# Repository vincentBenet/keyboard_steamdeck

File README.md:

# keyboard_steamdeck

[Github](https://github.com/vincentBenet/keyboard_steamdeck)
[Author: Vincent Bénet](https://github.com/vincentBenet)

## Introduction

This project aim to create a minimalist custom keyboard using standard keycaps.
The goal is to have no keys restriction compare to a 120% keyboard.

## Features
Bellow a list of features of this keyboard:

    - All keys from 120% keyboards (Directionnal arrows, del, backspace, G keys)
    
    - Possibility to switch from AZERTY to QWERTY
    
    - 8 programables macro-G-keys
    
    - Up to 6 differents keys mapped on one switch (FN1, FN2, FN3, FN4, SHIFT, Simple press)
    
    - Reprogramming possibility of firmware
    
    - Electro Static Protection using TVS USB
    
    - Very low energy consumption using STM32L0 Chip
    
    - Case-material versatile (Wood, Aluminium, Inox, plastic, ...) (2mm cutted sheet)
    
## Layout

[Edit - Layout](http://www.keyboard-layout-editor.com/##@@_c=%23000000&t=%23ffffff&f:2%3B&=%F0%9F%94%8F%0A%E2%8F%8F%EF%B8%8F%0A%E2%9D%8C%0A%E2%8C%A8%0A%0A%0A%0A%0A%0AESC&_c=%23ff3b00&t=%234000ff%0A%2300ffde%0A%23337000&f:3%3B&=1%0AF1%0A%2F&%0A%C2%B2%0A%0A%0A%0A%0A%0AA&_c=%23000000&t=%23ffffff%0A%2300ffde%3B&=2%0AF2%0A%C3%A9%0A~%0A%0A%0A%0A%0A%0AZ&_c=%23ff3b00&t=%234000ff%0A%2300ffde%0A%23337000%3B&=3%0AF3%0A%22%0A%23%0A%0A%0A%0A%0A%0AE&=4%0AF4%0A'%0A%7B%0A%0A%0A%0A%0A%0AR&=5%0AF5%0A(%0A%5B%0A%0A%0A%0A%0A%0AT&=6%0AF6%0A-%0A%7C%0A%0A%0A%0A%0A%0AY&=7%0AF7%0A%C3%A8%0A%60%0A%0A%0A%0A%0A%0AU&=8%0AF8%0A%2F_%0A%5C%0A%0A%0A%0A%0A%0A%E2%85%A0&=9%0AF9%0A%C3%A7%0A%5E%0A%0A%0A%0A%0A%0AO&=0%0AF10%0A%C3%A0%0A%2F@%0A%0A%0A%0A%0A%0AP%3B&@_c=%233d3d3d&t=%23ffffff&a:7&f:9%3B&=%E2%87%84&_c=%23000000&a:4&f:3%3B&=(%0A%3C%0A%5B%0A%7B%0A%0A%0A%0A%0A%0AQ&=%C2%B6%0A-%0A%E2%84%B9%EF%B8%8F%0A%2F_%0A%0A%0A%0A%0A%0AS&=)%0A%3E%0A%5D%0A%7D%0A%0A%0A%0A%0A%0AD&_c=%230068ff&t=%23fff300%0A%0A%0A%0A%0A%0A%0A%0A%0A%2300ff17%3B&=G1%0AG3%0AG2%0AG4%0A%0A%0A%0A%0A%0AF&_t=%23a32424%0A%0A%0A%23ff0000%0A%0A%0A%0A%0A%0A%2300ff17%3B&=%E2%8F%BA%0A%F0%9F%8E%AC%0A%F0%9F%8E%A4%0A%E2%8F%B9%0A%0A%0A%0A%0A%0AG&_t=%23fff300%0A%0A%0A%0A%0A%0A%0A%0A%0A%2300ff17%3B&=G5%0AG7%0AG6%0AG8%0A%0A%0A%0A%0A%0AH&_c=%233c4225&t=%23ffffff%3B&=%C2%A5%0A%C3%B9%0A%C2%A4%0A%C2%B5%0A%0A%0A%0A%0A%0AJ&_c=%23a7a800&t=%23000000%3B&=%E2%82%AC%0A%C2%A2%0A$%0A%C2%A3%0A%0A%0A%0A%0A%0AK&_c=%23ff3b00&t=%23000000%0A%2300ffde%0A%23337000%3B&=%C2%B0%0AF12%0A%2F=%0A%7D%0A%0A%0A%0A%0A%0AL&=+%0AF11%0A)%0A%5D%0A%0A%0A%0A%0A%0AM%3B&@_c=%233d3d3d&t=%23ffffff&a:7&f:9%3B&=%E2%86%91&_c=%23ffa31a&t=%23000000&a:4&f:3%3B&=%E2%8C%A7%0A%C2%AB%0A%F0%9F%94%9E%0A%C2%BB%0A%0A%0A%0A%0A%0AW&_c=%238c1b00%3B&=%E2%9E%97%0A%E2%9E%96%0A%E2%9C%96%EF%B8%8F%0A%E2%9E%95%0A%0A%0A%0A%0A%0AX&_c=%23ffffff%3B&=%2F=%0A%EF%BC%85%0A%3F%0A%EF%B9%90%0A%0A%0A%0A%0A%0AC&=%C2%BF%0A%C3%A6%0A%E2%80%A7%0A%EF%BC%9B%0A%0A%0A%0A%0A%0AV&=%5C%0A%7C%0A%2F%2F%0A%EF%BC%9A%0A%0A%0A%0A%0A%0AB&=%E2%80%9C%0A%E2%80%9E%0A%C2%A7%0A!%0A%0A%0A%0A%0A%0AN&_c=%230bff00%3B&=%E2%8F%AB%0A%F0%9F%94%86%0A%F0%9F%92%BE%0A%F0%9F%94%8A%0A%0A%0A%0A%0A%0A%E2%96%B2&_c=%23ff00e8%3B&=%F0%9F%93%B7%0A%E2%AC%91%0A%F0%9F%94%91%0A%F0%9F%94%92%0A%0A%0A%0A%0A%0A%E2%8F%8E&_c=%23000000&t=%23ffffff%3B&=%E2%8C%9C%0A%0A%0A%0A%0A%0A%0A%0A%0AFN1&=%0A%0A%E2%8C%9D%0A%0A%0A%0A%0A%0A%0AFN2%3B&@_c=%23878787&a:7%3B&=CRTL&_c=%23000000&f:9%3B&=%F0%9F%97%BA%EF%B8%8F&_c=%238e8e8e&f:3%3B&=ALT&_c=%23000bff&a:4%3B&=%E2%9C%82%EF%B8%8F%0A%F0%9F%93%9D%0A%F0%9F%93%8B%0A%F0%9F%93%8C%0A%0A%0A%0A%0A%0A%E2%80%95&_c=%23ff00e8&t=%23000000%3B&=%E2%A4%BA%0A%E2%98%8E%0A%E2%8F%AE%0A%E2%8F%B9%0A%0A%0A%0A%0A%0A%E2%8C%AB&=%E2%A4%BC%0A%E2%9A%99%EF%B8%8F%0A%E2%8F%AD%0A%E2%8F%AF%0A%0A%0A%0A%0A%0A%E2%8C%A6&_c=%230bff00%3B&=%E2%8F%AA%0A%F0%9F%8C%93%0A%E2%9C%88%0A%F0%9F%94%87%0A%0A%0A%0A%0A%0A%E2%97%84&=%E2%8F%AC%0A%F0%9F%94%85%0A%F0%9F%93%85%0A%F0%9F%94%89%0A%0A%0A%0A%0A%0A%E2%96%BC&=%E2%8F%A9%0A%E2%9C%89%0A%F0%9F%93%B6%0A%E2%99%AB%0A%0A%0A%0A%0A%0A%E2%96%BA&_c=%23000000&t=%23ffffff%3B&=%0A%E2%8C%9E%0A%0A%0A%0A%0A%0A%0A%0AFN3&=%0A%0A%0A%E2%8C%9F%0A%0A%0A%0A%0A%0AFN4)

## Model 3D

## Schematic

## Routing

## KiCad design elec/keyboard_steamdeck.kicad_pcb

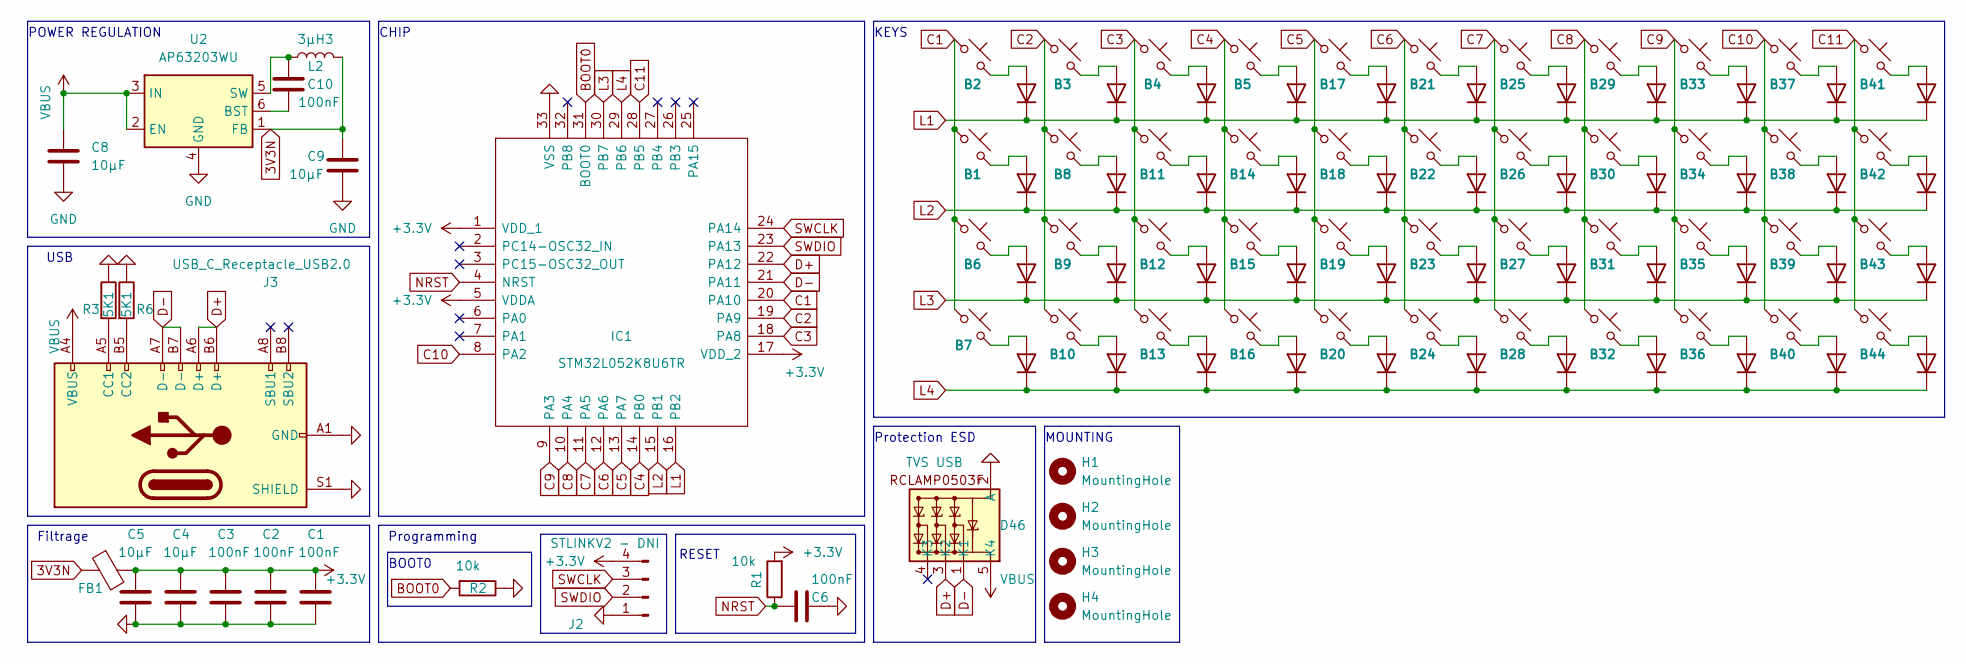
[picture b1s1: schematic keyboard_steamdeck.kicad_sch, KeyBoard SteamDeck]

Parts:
B1, B2, B3, B4, B5, B6, B7, B8, B9, B10, B11, B12, B13, B14, B15, B16, B17, B18, B19, B20, B21, B22, B23, B24, B25, B26, B27, B28, B29, B30, B31, B32, B33, B34, B35, B36, B37, B38, B39, B40, B41, B42, B43, B44: MX_SW_solder - DNI; SW_Cherry_MX_1.00u_PCB; MPN MX2A-L1NN
C1, C2, C3, C6, C10: 100nF; C_0402_1005Metric; MPN CC0402KRX7R8BB104
C4, C5, C8, C9: 10µF; C_0805_2012Metric; MPN CAP0805 X7R 10UF 10% 16V
D1, D2, D3, D4, D5, D6, D7, D8, D9, D10, D11, D12, D13, D14, D15, D16, D17, D18, D19, D20, D21, D22, D23, D24, D25, D26, D27, D28, D29, D30, D31, D32, D33, D34, D35, D36, D37, D38, D39, D40, D41, D42, D43, D44: 1N4148WX-TP; D_SOD-323_HandSoldering; MPN 1N4148WX-TP
D46: TVS USB; SOT-353_SC-70-5; MPN RCLAMP0503F.TCT
FB1: FerriteBead; R_0402_1005Metric; MPN PE-0603PFB121ST
H1, H2, H3, H4: MountingHole; MountingHole_3.2mm_M3
IC1: STM32L052K8U6TR; UFQFPN32-5x5mm; MPN STM32L052K8U6TR
J2: STLINKV2 - DNI; PinHeader_1x04_P2.54mm_Vertical; MPN 61300411121
J3: USB_C_Receptacle_USB2.0; USB C 2130830005; MPN 2130830005
L2: 3µH3; R_0805_2012Metric; MPN MLZ2012N3R3LT000
R1, R2: 10k; R_0402_1005Metric; MPN ERA-2AEB103X
R3, R6: 5K1; R_0402_1005Metric; MPN RN73R1ETTP5101B25
U2: AP63203WU; TSOT-23-6; MPN AP63203WU-7

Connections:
3V3N: C9.1, FB1.1, L2.2, U2.1 (FB)
+3.3V: C1.2, C2.2, C3.2, C4.2, C5.2, FB1.2, IC1.1 (VDD_1), IC1.5 (VDDA), IC1.17 (VDD_2), J2.4, R1.2
BOOT0: IC1.31 (BOOT0), R2.2
C1: B1.1, B2.1, B6.1, B7.1, IC1.20 (PA10)
C2: B3.1, B8.1, B9.1, B10.1, IC1.19 (PA9)
C3: B4.1, B11.1, B12.1, B13.1, IC1.18 (PA8)
C4: B5.1, B14.1, B15.1, B16.1, IC1.14 (PB0)
C5: B17.1, B18.1, B19.1, B20.1, IC1.13 (PA7)
C6: B21.1, B22.1, B23.1, B24.1, IC1.12 (PA6)
C7: B25.1, B26.1, B27.1, B28.1, IC1.11 (PA5)
C8: B29.1, B30.1, B31.1, B32.1, IC1.10 (PA4)
C9: B33.1, B34.1, B35.1, B36.1, IC1.9 (PA3)
C10: B37.1, B38.1, B39.1, B40.1, IC1.8 (PA2)
C11: B41.1, B42.1, B43.1, B44.1, IC1.28 (PB5)
D+: D46.3 (K2), IC1.22 (PA12), J3.A6 (D+), J3.B6 (D+)
D-: D46.1 (K1), IC1.21 (PA11), J3.A7 (D-), J3.B7 (D-)
GND: C1.1, C2.1, C3.1, C4.1, C5.1, C6.1, C8.2, C9.2, D46.2 (A), IC1.33 (VSS), J2.1, J3.A1 (GND), J3.A12 (GND), J3.B1 (GND), J3.B12 (GND), J3.S1 (SHIELD), R2.1, R3.1, R6.1, U2.4 (GND)
L1: D11.1 (K), D12.1 (K), D13.1 (K), D14.1 (K), D15.1 (K), D16.1 (K), D17.1 (K), D18.1 (K), D19.1 (K), D20.1 (K), D41.1 (K), IC1.16 (PB2)
L2: D1.1 (K), D2.1 (K), D3.1 (K), D4.1 (K), D5.1 (K), D6.1 (K), D7.1 (K), D8.1 (K), D9.1 (K), D10.1 (K), D42.1 (K), IC1.15 (PB1)
L3: D21.1 (K), D23.1 (K), D25.1 (K), D27.1 (K), D29.1 (K), D31.1 (K), D33.1 (K), D35.1 (K), D37.1 (K), D39.1 (K), D43.1 (K), IC1.30 (PB7)
L4: D22.1 (K), D24.1 (K), D26.1 (K), D28.1 (K), D30.1 (K), D32.1 (K), D34.1 (K), D36.1 (K), D38.1 (K), D40.1 (K), D44.1 (K), IC1.29 (PB6)
NRST: C6.2, IC1.4 (NRST), R1.1
unnamed: B22.2, D1.2 (A)
unnamed: B26.2, D2.2 (A)
unnamed: B30.2, D3.2 (A)
unnamed: B34.2, D4.2 (A)
unnamed: B38.2, D5.2 (A)
unnamed: B1.2, D6.2 (A)
unnamed: B8.2, D7.2 (A)
unnamed: B11.2, D8.2 (A)
unnamed: B14.2, D9.2 (A)
unnamed: B18.2, D10.2 (A)
unnamed: B2.2, D11.2 (A)
unnamed: B3.2, D12.2 (A)
unnamed: B4.2, D13.2 (A)
unnamed: B5.2, D14.2 (A)
unnamed: B17.2, D15.2 (A)
unnamed: B21.2, D16.2 (A)
unnamed: B25.2, D17.2 (A)
unnamed: B29.2, D18.2 (A)
unnamed: B33.2, D19.2 (A)
unnamed: B37.2, D20.2 (A)
unnamed: B6.2, D21.2 (A)
unnamed: B7.2, D22.2 (A)
unnamed: B9.2, D23.2 (A)
unnamed: B10.2, D24.2 (A)
unnamed: B12.2, D25.2 (A)
unnamed: B13.2, D26.2 (A)
unnamed: B15.2, D27.2 (A)
unnamed: B16.2, D28.2 (A)
unnamed: B19.2, D29.2 (A)
unnamed: B20.2, D30.2 (A)
unnamed: B23.2, D31.2 (A)
unnamed: B24.2, D32.2 (A)
unnamed: B27.2, D33.2 (A)
unnamed: B28.2, D34.2 (A)
unnamed: B31.2, D35.2 (A)
unnamed: B32.2, D36.2 (A)
unnamed: B35.2, D37.2 (A)
unnamed: B36.2, D38.2 (A)
unnamed: B39.2, D39.2 (A)
unnamed: B40.2, D40.2 (A)
unnamed: B41.2, D41.2 (A)
unnamed: B42.2, D42.2 (A)
unnamed: B43.2, D43.2 (A)
unnamed: B44.2, D44.2 (A)
unnamed: J3.A5 (CC1), R3.2
unnamed: J3.B5 (CC2), R6.2
unnamed: C10.2, U2.6 (BST)
unnamed: C10.1, L2.1, U2.5 (SW)
SWCLK: IC1.24 (PA14), J2.3
SWDIO: IC1.23 (PA13), J2.2
VBUS: C8.1, D46.5 (K4), J3.A4 (VBUS), J3.A9 (VBUS), J3.B4 (VBUS), J3.B9 (VBUS), U2.2 (EN), U2.3 (IN)

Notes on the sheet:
CHIP
Filtrage
KEYS
MOUNTING
POWER REGULATION
RESET
BOOT0
Protection ESD
USB
Programming

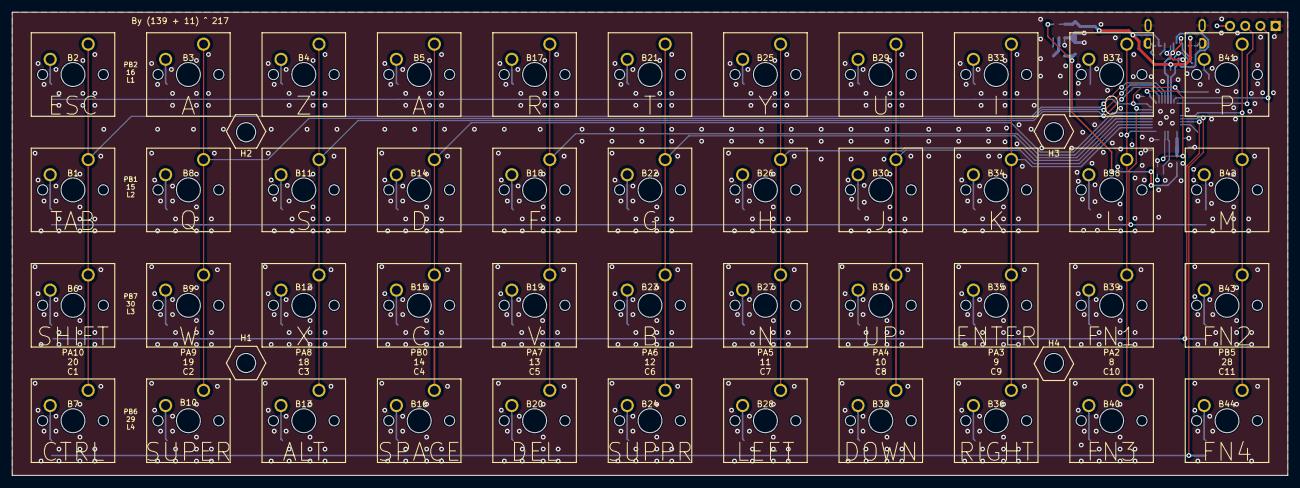
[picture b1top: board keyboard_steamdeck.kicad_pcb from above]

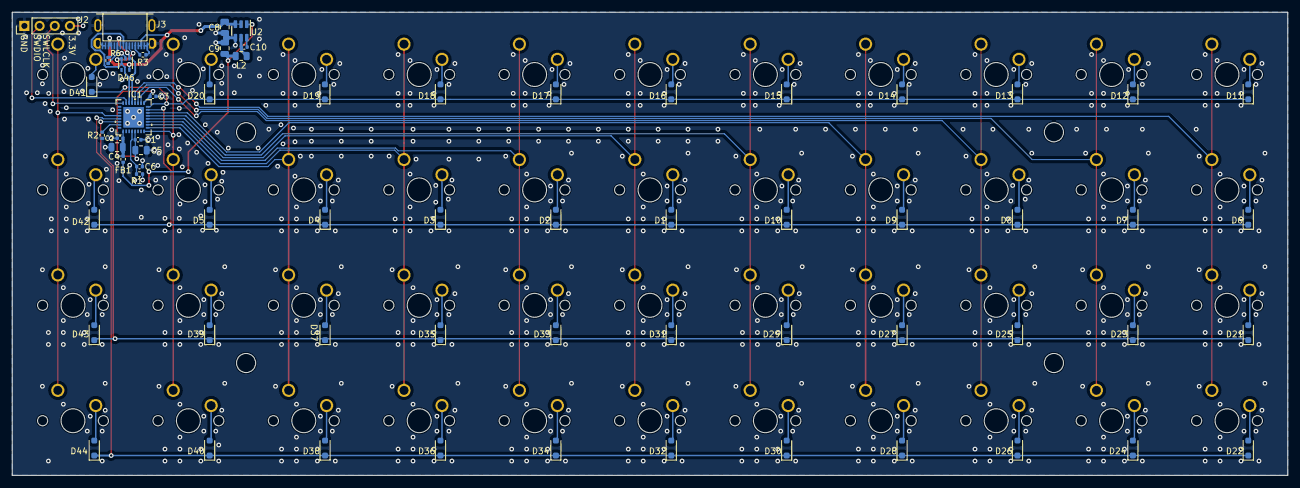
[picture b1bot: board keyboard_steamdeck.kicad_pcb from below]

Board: 4 copper layers, 213.4 x 77.5 mm, 112 parts (64 on the bottom side), 73 nets.

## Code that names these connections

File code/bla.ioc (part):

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Mcu.Name=STM32L052K(6-8)Ux
Mcu.Package=UFQFPN32
Mcu.UserName=STM32L052K8Ux
PA10.Signal=GPIO_Output
PA11.Mode=Device
PA11.Signal=USB_DM
PA12.Mode=Device
PA12.Signal=USB_DP
PA13.Mode=Serial_Wire
PA13.Signal=SYS_SWDIO
PA14.Mode=Serial_Wire
PA14.Signal=SYS_SWCLK
PA2.Signal=GPIO_Output
PA3.Signal=GPIO_Output
PA4.Signal=GPIO_Output
PA5.Signal=GPIO_Output
PA6.Signal=GPIO_Output
PA7.Signal=GPIO_Output
PA8.Signal=GPIO_Output
PA9.Signal=GPIO_Output
PB0.Signal=GPIO_Output
PB1.GPIOParameters=GPIO_PuPd
PB1.GPIO_PuPd=GPIO_PULLDOWN
PB1.Signal=GPIO_Input
PB2.GPIOParameters=GPIO_PuPd
PB2.GPIO_PuPd=GPIO_PULLDOWN
PB2.Signal=GPIO_Input
PB5.Signal=GPIO_Output
PB6.GPIOParameters=GPIO_PuPd
PB6.GPIO_PuPd=GPIO_PULLDOWN
PB6.Signal=GPIO_Input
PB7.GPIOParameters=GPIO_PuPd
PB7.GPIO_PuPd=GPIO_PULLDOWN
PB7.Signal=GPIO_Input
RCC.SYSCLKFreq_VALUE=24000000
RCC.SYSCLKSource=RCC_SYSCLKSOURCE_PLLCLK
board=custom

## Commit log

2023-10-10 corrections
2023-10-11 Finish
2023-10-11 readme
2023-10-13 ready to order PCB
2023-11-25 add_code
2024-01-09 working_key_scan
2024-01-31 working_keyboard
2024-02-10 Keyboard in FR + True repeating keys
2024-02-10 fix FN infinite repeat
2024-02-19 almost working firmaware
2024-02-19 WIP still some bugs
2024-02-23 working keyboard
2024-03-18 save
